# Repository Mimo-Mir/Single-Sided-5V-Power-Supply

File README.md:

# Single-Sided 5V Regulated Power Supply

A compact **single-sided 5V regulated linear power supply** designed using **KiCad 9** and built around the **LM7805 voltage regulator**.

This project was developed as part of my PCB design learning journey to gain hands-on experience with the complete hardware development workflow—from schematic capture and PCB layout to electrical verification, 3D visualization, Gerber generation, and project documentation.

In addition to PCB design, this project demonstrates the basic design principles of a regulated linear power supply, including rectification, filtering, voltage regulation, and component selection.

---

# Project Preview

## PCB Layout

## 3D View (Front)

## 3D View (Back)

## Schematic

---

# About This Project

The primary objective of this project was to learn professional PCB design using **KiCad 9** while designing a simple regulated power supply suitable for educational and low-power embedded applications.

Although the electrical circuit is based on the widely used **LM7805 linear voltage regulator**, the project focuses on understanding the complete PCB development process, including:

- Electronic schematic design
- Component selection
- Footprint assignment
- PCB layout
- Manual routing
- Electrical verification
- Manufacturing file generation
- Hardware project documentation
- Version control using Git and GitHub

The completed board is designed as a **single-sided through-hole PCB**, making it easy to assemble, inspect, and understand for students, beginners, and electronics hobbyists.

---

# Design Objectives

The project was developed with the following objectives:

- Design a functional regulated 5V power supply using the LM7805.
- Practice schematic capture using KiCad 9.
- Learn proper footprint assignment.
- Design a manufacturable single-sided PCB.
- Perform ERC (Electrical Rules Check) and DRC (Design Rules Check).
- Generate fabrication-ready Gerber files.
- Document the complete design process professionally.
- Understand the importance of power supply filtering and voltage regulation.

---

# Features

- Single-sided PCB design
- Through-hole components (easy to solder)
- Regulated 5V DC output using LM7805
- Full-wave bridge rectifier
- Large input smoothing capacitor
- LM7805 datasheet-recommended bypass capacitors
- Power indicator LED
- Manual PCB routing
- Ground copper pour
- ERC verified
- DRC verified
- 3D PCB visualization
- Manufacturing-ready Gerber files
- Complete GitHub documentation

---

# Design Specifications

| Parameter | Value |
|-----------|-------|
| Input Supply | 9V AC Transformer |
| Rectifier | Full-Wave Bridge Rectifier |
| Output Voltage | 5V DC |
| Maximum Output Current | **500 mA** |
| Voltage Regulator | LM7805 |
| Main Filter Capacitor (C1) | **3300 µF** |
| Input Bypass Capacitor (C2) | **0.33 µF** |
| Output Bypass Capacitor (C3) | **0.1 µF** |
| PCB Type | Single-Sided |
| Mounting Style | Through-Hole (THT) |
| PCB Design Software | KiCad 9 |
| Routing | Manual |
| Ground Plane | Copper Pour |
| Manufacturing Files | Gerber |

---

# Design Assumptions

The following assumptions were used during the design of this project:

- Input supplied from a **9V AC transformer**.
- Maximum continuous output current of **500 mA**.
- Ambient operating temperature of approximately **25°C**.
- Intended for low-power embedded systems and educational applications.
- Designed as a linear regulated power supply where efficiency is secondary to simplicity and ease of understanding.

These assumptions are important because component selection, filtering, thermal performance, and regulator operation depend on the expected load conditions.

---

# Project Overview

The circuit converts a **9V AC input** into a regulated **5V DC output** through four main stages:

## 1. AC to DC Rectification

A full-wave bridge rectifier converts the incoming AC voltage into pulsating DC.

---

## 2. Input Filtering

A **3300 µF electrolytic capacitor (C1)** smooths the rectified voltage by reducing ripple before it reaches the voltage regulator.

This larger capacitor was selected to improve ripple performance for the intended **500 mA maximum output current**.

---

## 3. Voltage Regulation

An **LM7805 linear voltage regulator** provides a stable **5V DC output** over a range of load conditions.

The regulator includes internal:

- Current limiting
- Thermal shutdown
- Safe operating area protection

making it suitable for educational and low-power applications.

---

## 4. High-Frequency Decoupling

To improve regulator stability, two ceramic bypass capacitors are placed close to the LM7805:

- **0.33 µF (C2)** at the regulator input
- **0.1 µF (C3)** at the regulator output

These capacitor values follow the recommendations provided in the LM7805 datasheet and help suppress high-frequency noise while improving transient response.

---

# Components Used

| Component | Quantity | Purpose |
|-----------|:-------:|---------|
| LM7805 Voltage Regulator | 1 | Regulates the output to a stable 5V DC |
| Bridge Rectifier | 1 | Converts AC input into pulsating DC |
| 3300 µF Electrolytic Capacitor (C1) | 1 | Smooths the rectified voltage and reduces ripple |
| 0.33 µF Ceramic Capacitor (C2) | 1 | LM7805 input bypass capacitor for stability |
| 0.1 µF Ceramic Capacitor (C3) | 1 | LM7805 output bypass capacitor for stability |
| 330 Ω Resistor | 1 | Limits LED current |
| 2-Pin Screw Terminal | 2 | Input and output power connections |

---

# Why These Components?

### LM7805

The LM7805 is a widely used linear voltage regulator capable of providing a regulated **5V output** with minimal external components. It also includes built-in thermal shutdown and current limiting, making it an excellent choice for beginner-friendly power supply designs.

---

### Bridge Rectifier

The bridge rectifier converts the incoming **9V AC** into pulsating DC, allowing the regulator to operate from a transformer-based AC supply.

---

### 3300 µF Electrolytic Capacitor

The large electrolytic capacitor significantly reduces ripple voltage after rectification.

For the intended **500 mA load**, a higher capacitance improves voltage smoothing and helps maintain sufficient input voltage for proper LM7805 regulation.

---

### 0.33 µF and 0.1 µF Ceramic Capacitors

These capacitors are placed close to the regulator input and output pins to improve high-frequency filtering and regulator stability.

Their values follow the recommendations provided in the LM7805 datasheet.
---

### Screw Terminals

The screw terminals provide secure and reusable connections for both the AC input and regulated DC output.

# Electrical Design Considerations

Although this project was primarily created to learn PCB design, several engineering considerations were incorporated to improve the reliability and stability of the power supply.

The design follows the typical architecture of a linear regulated power supply:

```text
9V AC
   │
Bridge Rectifier
   │
3300 µF Filter Capacitor
   │
0.33 µF Bypass Capacitor
   │
LM7805 Voltage Regulator
   │
0.1 µF Bypass Capacitor
   │
5V DC Output
```

Each stage performs a specific function to convert the AC input into a clean and regulated 5V DC output.

---

# Design Calculations

## 1. Rectified DC Voltage

The circuit is designed to operate from a **9V AC transformer**.

The peak voltage after rectification can be approximated as:

**Vpeak = VAC × √2**

For a 9V AC input:

```
Vpeak ≈ 9 × 1.414
      ≈ 12.7 V
```

After accounting for the voltage drop across the bridge rectifier (approximately 1.4V), the capacitor charges to approximately:

```
VDC ≈ 11.3 V
```

This provides sufficient input voltage for the LM7805 to regulate the output to 5V.

---

## 2. Input Filter Capacitor Selection

After rectification, the voltage contains ripple.

A large electrolytic capacitor stores energy between the peaks of the rectified waveform, reducing ripple voltage before the regulator.

For this design, a **3300 µF capacitor** was selected.

Compared to smaller values, the larger capacitance provides:

- Lower ripple voltage
- Improved load regulation
- Better support for the intended 500 mA load
- Increased stability during transient current demands

---

## 3. Bypass Capacitors

Two ceramic capacitors are used near the LM7805.

### Input Capacitor (C2)

Value:

```
0.33 µF
```

Purpose:

- Filters high-frequency noise
- Improves regulator stability
- Recommended by the LM7805 datasheet

---

### Output Capacitor (C3)

Value:

```
0.1 µF
```

Purpose:

- Prevents high-frequency oscillation
- Improves transient response
- Reduces output noise
- Recommended by the LM7805 datasheet

Both capacitors are placed as close as possible to the regulator pins to maximize their effectiveness.

---

# Thermal Considerations

The LM7805 is a **linear voltage regulator**, meaning excess voltage is dissipated as heat.

The power dissipated by the regulator can be estimated using:

```
P = (Vin − Vout) × Iout
```

Assuming:

- Input voltage ≈ 11.3V DC
- Output voltage = 5V
- Maximum output current = 500 mA

```
P = (11.3 − 5) × 0.5

P ≈ 3.15 W
```

A power dissipation of approximately **3 W** can cause the regulator to become hot during continuous operation.

For sustained operation at the maximum rated current, a suitable heatsink is recommended to maintain safe operating temperatures.

---

# Why a Linear Regulator?

Several voltage regulation methods are available, including switching regulators and linear regulators.

For this project, the **LM7805** was selected because it offers:

- Simple circuit design
- Minimal external components
- Low cost
- High reliability
- Excellent educational value

Although switching regulators provide much higher efficiency, the LM7805 is easier to understand and is commonly used when learning basic power supply design.

---

# PCB Design Workflow

The PCB was developed using the same workflow commonly followed in professional PCB design.

The complete process consisted of:

1. Creating the schematic.
2. Selecting appropriate components.
3. Assigning footprints.
4. Importing the schematic into the PCB editor.
5. Arranging components for efficient routing.
6. Manually routing all traces.
7. Creating a ground copper pour.
8. Running ERC and DRC verification.
9. Inspecting the PCB using KiCad's 3D Viewer.
10. Generating Gerber files for fabrication.

Following this workflow helped ensure that the design was electrically correct, manufacturable, and well documented.

---

# 1. Schematic Design

The project began by creating the complete circuit schematic in **KiCad 9**.

During this stage:

- All electronic components were selected.
- Electrical connections were completed.
- Power symbols were added.
- Net labels were used where appropriate.
- Component values were assigned.
- Electrical connectivity was verified.

A clean schematic is the foundation of a reliable PCB design and helps reduce errors during later stages of development.

---

# 2. Footprint Assignment

Each schematic symbol was assigned an appropriate physical footprint before PCB layout.

The selected footprints match standard through-hole components, making assembly straightforward for beginners.

The assigned footprints include:

- TO-220 package for the LM7805
- Through-hole electrolytic capacitors
- Ceramic disc capacitors
- LED
- Resistors
- Screw terminals
- Bridge rectifier

Correct footprint assignment ensures that the physical components fit properly during PCB assembly.

---

# 3. Component Placement

Once the PCB was created from the schematic, components were arranged before routing.

The placement process focused on:

- Keeping related components close together.
- Minimizing unnecessary trace lengths.
- Placing bypass capacitors close to the LM7805.
- Improving routing efficiency.
- Maintaining adequate spacing for soldering and inspection.

Proper placement significantly simplified the routing process and improved the overall appearance of the PCB.

---

# 4. Manual Routing

Because the PCB is single-sided, all traces were manually routed on one copper layer.

Manual routing provided better control over:

- Trace length
- Routing clarity
- Component accessibility
- Manufacturing simplicity

Several component placements were adjusted during routing to achieve a clean and practical layout.

The final routing avoids unnecessary bends and keeps the board easy to understand for educational purposes.

# 5. Ground Copper Pour

After completing the routing, a **Ground (GND) Copper Pour** was added across the PCB.

Using a ground plane offers several advantages:

- Reduces unused copper areas.
- Improves grounding throughout the board.
- Simplifies ground routing.
- Can slightly improve heat distribution.
- Provides a cleaner and more professional PCB layout.

After creating the copper pour, the filled zones were updated to ensure all ground connections were electrically connected.

---

# 6. Electrical Rules Check (ERC)

Before PCB layout, an **Electrical Rules Check (ERC)** was performed.

ERC verifies the logical correctness of the schematic by checking for issues such as:

- Missing electrical connections
- Unconnected pins
- Incorrect power connections
- Missing power flags
- Electrical rule violations

Any reported issues were reviewed and corrected before continuing with the PCB layout.

Running ERC helped ensure that the schematic accurately represented the intended electrical circuit.

---

# 7. Design Rules Check (DRC)

After completing the PCB layout, a **Design Rules Check (DRC)** was performed.

Unlike ERC, which validates the schematic, DRC checks the physical PCB layout.

The following items were verified:

- Trace clearances
- Minimum spacing between pads
- Track width violations
- Overlapping footprints
- Board outline integrity
- Manufacturing rule compliance

Passing DRC provides confidence that the PCB is suitable for fabrication.

---

# 8. 3D Verification

Before generating manufacturing files, the PCB was inspected using **KiCad's 3D Viewer**.

The 3D inspection was used to verify:

- Component orientation
- Footprint placement
- Silkscreen readability
- Mechanical appearance
- Overall board layout

This step helps identify placement or orientation issues that may not be obvious in the 2D PCB editor.

---

# 9. Gerber File Generation

The final stage of the project was generating the manufacturing files required for PCB fabrication.

The generated files include:

- Top Copper Layer
- Bottom Copper Layer
- Top Silkscreen
- Bottom Silkscreen
- Top Solder Mask
- Bottom Solder Mask
- Edge Cuts
- Drill Files
- Gerber Job File

These files are included in the **gerbers/** directory and are ready for submission to a PCB manufacturer.

---

# Testing

Although this project was primarily created as a PCB design learning exercise, the circuit was designed using standard linear power supply design practices.

The following electrical characteristics are expected:

| Parameter | Expected Value |
|-----------|---------------:|
| Input Voltage | 9V AC |
| Output Voltage | 5V DC |
| Maximum Output Current | 500 mA |
| Voltage Regulation | Approximately ±5% |
| Regulator | LM7805 |

Future revisions of the project may include measured performance data such as:

- Output voltage under different loads
- Ripple voltage measurements
- Thermal measurements of the LM7805
- Efficiency calculations
- Load regulation
- Line regulation

---

# Design Limitations

Like any engineering design, this project has certain limitations.

- Designed primarily for educational purposes.
- Intended for low-power embedded applications.
- Maximum recommended continuous output current is **500 mA**.
- Linear voltage regulators are less efficient than switching regulators.
- Excess input voltage is dissipated as heat by the LM7805.
- Continuous operation near maximum load requires an appropriate heatsink.

Understanding these limitations is an important part of engineering design and helps determine whether the circuit is suitable for a particular application.

---

# Repository Structure

The repository is organized to separate documentation, PCB design files, and manufacturing outputs.

```text
Single-Sided-5V-Power-Supply/
│
├── Docs/
│   ├── schematic.png
│   ├── pcb-layout.png
│   ├── pcb-3d-front.png
│   └── pcb-3d-back.png
│
├── gerbers/
│   ├── *.gbr
│   ├── *.drl
│   └── *.gbrjob
│
├── LICENSE
├── README.md
├── .gitignore
│
├── Single-Sided 5V Power Supply.kicad_pro
├── Single-Sided 5V Power Supply.kicad_sch
└── Single-Sided 5V Power Supply.kicad_pcb
```

---

# Results

This project successfully demonstrates the complete workflow involved in designing a simple regulated power supply PCB using KiCad.

Through this project I gained practical experience with:

- Electronic schematic design
- PCB layout techniques
- Component footprint assignment
- Manual PCB routing
- Ground plane implementation
- ERC verification
- DRC verification
- 3D PCB inspection
- Gerber generation
- Git version control
- GitHub project documentation

Although the electrical circuit itself is relatively simple, completing the entire hardware development workflow provided valuable practical experience that extends beyond circuit design alone.

# Challenges & Lessons Learned

Every hardware project presents unique challenges, and this project was no exception. While the electrical circuit is relatively simple, designing a manufacturable PCB and documenting the complete engineering workflow provided valuable practical experience.

## Challenges

### Learning the KiCad Workflow

One of the first challenges was understanding how each stage of PCB development connects together—from schematic capture to PCB layout, verification, and manufacturing.

Working through the complete workflow gave me a much better understanding of professional PCB development practices.

---

### Component Placement

Achieving a clean component placement required several iterations.

I learned that spending additional time arranging components before routing greatly simplifies PCB layout and results in a cleaner, more maintainable design.

---

### Single-Sided PCB Routing

Routing every connection on only one copper layer was one of the most challenging aspects of the project.

Because routing flexibility is limited on a single-sided PCB, I had to reposition components multiple times before reaching a layout that balanced functionality, manufacturability, and readability.

---

### Understanding Electrical Verification

Before this project, I had limited experience using ERC and DRC.

Through this design, I learned that:

- **ERC (Electrical Rules Check)** validates the schematic.
- **DRC (Design Rules Check)** validates the PCB layout.

Both are essential steps before manufacturing a PCB.

---

### Engineering Documentation

Another important lesson was learning that a good engineering project is not only about creating a working circuit but also about documenting the design decisions.

While improving this project, I expanded the documentation to include:

- Design assumptions
- Component selection
- Electrical design considerations
- Thermal analysis
- Design limitations

These additions make the project more useful for anyone reviewing or learning from the design.

---

# Lessons Learned

This project helped me develop practical experience with:

- PCB design using KiCad 9
- Electronic schematic capture
- Component footprint assignment
- Manual PCB routing
- Single-sided PCB design
- Ground copper pours
- ERC verification
- DRC verification
- 3D PCB inspection
- Gerber file generation
- Git version control
- GitHub project documentation
- Basic linear power supply design
- Engineering documentation

One of the biggest lessons I learned is that PCB design is an iterative engineering process.

Designing a reliable PCB requires much more than simply connecting components—it involves planning, verification, documentation, and continuous improvement.

---

# Future Improvements

Although this project successfully meets its educational objectives, several improvements could be made in future revisions.

Future versions may include:

- Reverse polarity protection using a protection diode or MOSFET.
- Input fuse for improved safety.
- Power switch.
- Mounting holes for enclosure installation.
- Improved silkscreen labels.
- Wider PCB traces for higher current capability.
- Larger copper areas around the voltage regulator for improved heat dissipation.
- Output test points for easier measurements.
- Thermal performance measurements under load.
- Ripple voltage measurements using an oscilloscope.
- Double-sided PCB version with optimized routing.
- Switching regulator version for higher efficiency.

These improvements would further increase the robustness and practical usability of the design.

---

# Skills Demonstrated

This project allowed me to develop and practice the following technical skills:

### Electronics

- Linear power supply design
- Bridge rectifier circuits
- Voltage regulation using LM7805
- Capacitor selection
- Basic thermal considerations

### PCB Design

- Schematic capture
- Footprint assignment
- PCB layout
- Manual routing
- Ground plane implementation
- Single-sided PCB design
- Design rule verification
- Manufacturing file generation

### Software

- KiCad 9
- Git
- GitHub

### Engineering Practice

- Hardware documentation
- Design verification
- Version control
- Project organization

---

# Tools Used

| Tool | Purpose |
|------|---------|
| KiCad 9 | Schematic Capture and PCB Design |
| Git | Version Control |
| GitHub | Project Hosting and Documentation |

---

# References

The following resources were used during the development of this project:

- LM7805 Voltage Regulator Datasheet
- KiCad 9 Official Documentation
- Basic Linear Power Supply Design References
- PCB Design Best Practices

---

# Acknowledgements

This project was completed as part of my ongoing journey to learn electronics and PCB design.

It provided valuable hands-on experience in the complete PCB development process, from schematic creation and PCB layout to verification, documentation, and manufacturing file generation.

The project also reinforced the importance of engineering documentation, design verification, and continuous improvement through technical feedback.

I look forward to applying these lessons to more advanced embedded systems, power electronics, and PCB design projects in the future.

---

# License

This project is licensed under the **MIT License**.

See the **LICENSE** file for more information.

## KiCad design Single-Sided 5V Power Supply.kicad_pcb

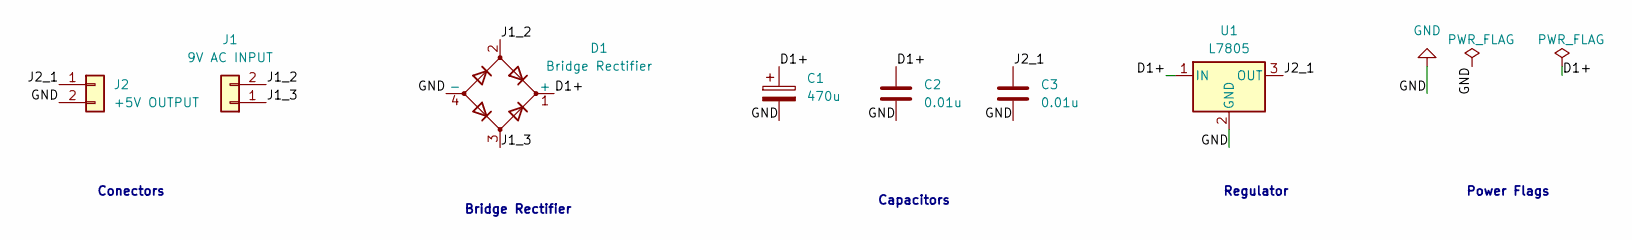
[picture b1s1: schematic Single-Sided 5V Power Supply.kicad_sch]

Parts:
C1: 470u; CP_Radial_D10.0mm_P5.00mm
C2, C3: 0.01u; C_Disc_D5.0mm_W2.5mm_P5.00mm
D1: Bridge Rectifier; Diode_Bridge_Round_D9.0mm
J1: 9V AC INPUT; TerminalBlock_Phoenix_MKDS-1,5-2-5.08_1x02_P5.08mm_Horizont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
J2: +5V OUTPUT; TerminalBlock_Phoenix_MKDS-1,5-2-5.08_1x02_P5.08mm_Horizont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
U1: L7805; TO-220-3_Vertical

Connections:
/D1+: C1.1, C2.1, D1.1 (+), U1.1 (IN)
/J1_2: D1.2, J1.2
/J1_3: D1.3, J1.1
/J2_1: C3.1, J2.1, U1.3 (OUT)
GND: C1.2, C2.2, C3.2, D1.4 (-), J2.2, U1.2 (GND)

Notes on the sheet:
Capacitors
Bridge Rectifier
Power Flags
Regulator
Conectors

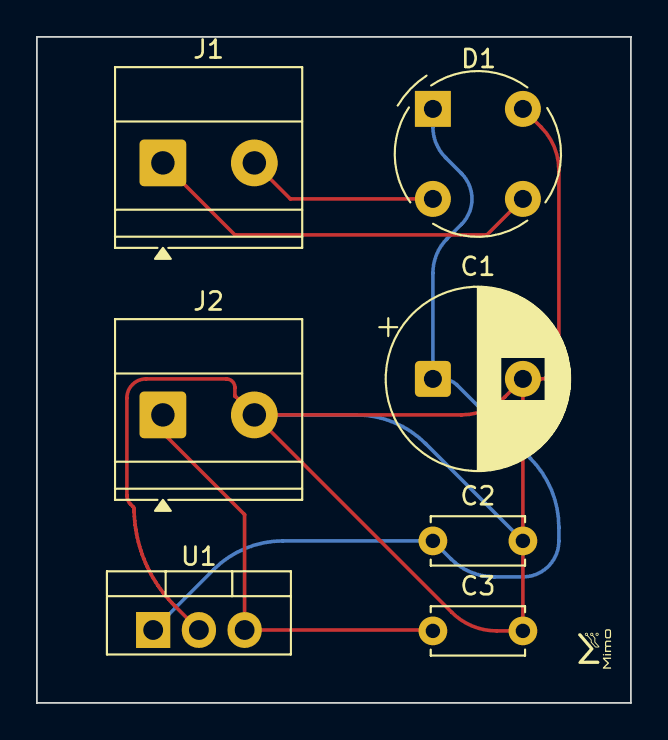
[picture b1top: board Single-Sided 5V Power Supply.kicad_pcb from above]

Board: 2 copper layers, 33.0 x 37.0 mm, 7 parts (0 on the bottom side), 5 nets.

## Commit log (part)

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2026-06-17 No Schematic and No PCB Layout
2026-06-24 Components are Added
2026-06-24 Componenets are Added

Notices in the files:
README.md:
License:
This project is licensed under the **MIT License**.
See the **LICENSE** file for more information.
